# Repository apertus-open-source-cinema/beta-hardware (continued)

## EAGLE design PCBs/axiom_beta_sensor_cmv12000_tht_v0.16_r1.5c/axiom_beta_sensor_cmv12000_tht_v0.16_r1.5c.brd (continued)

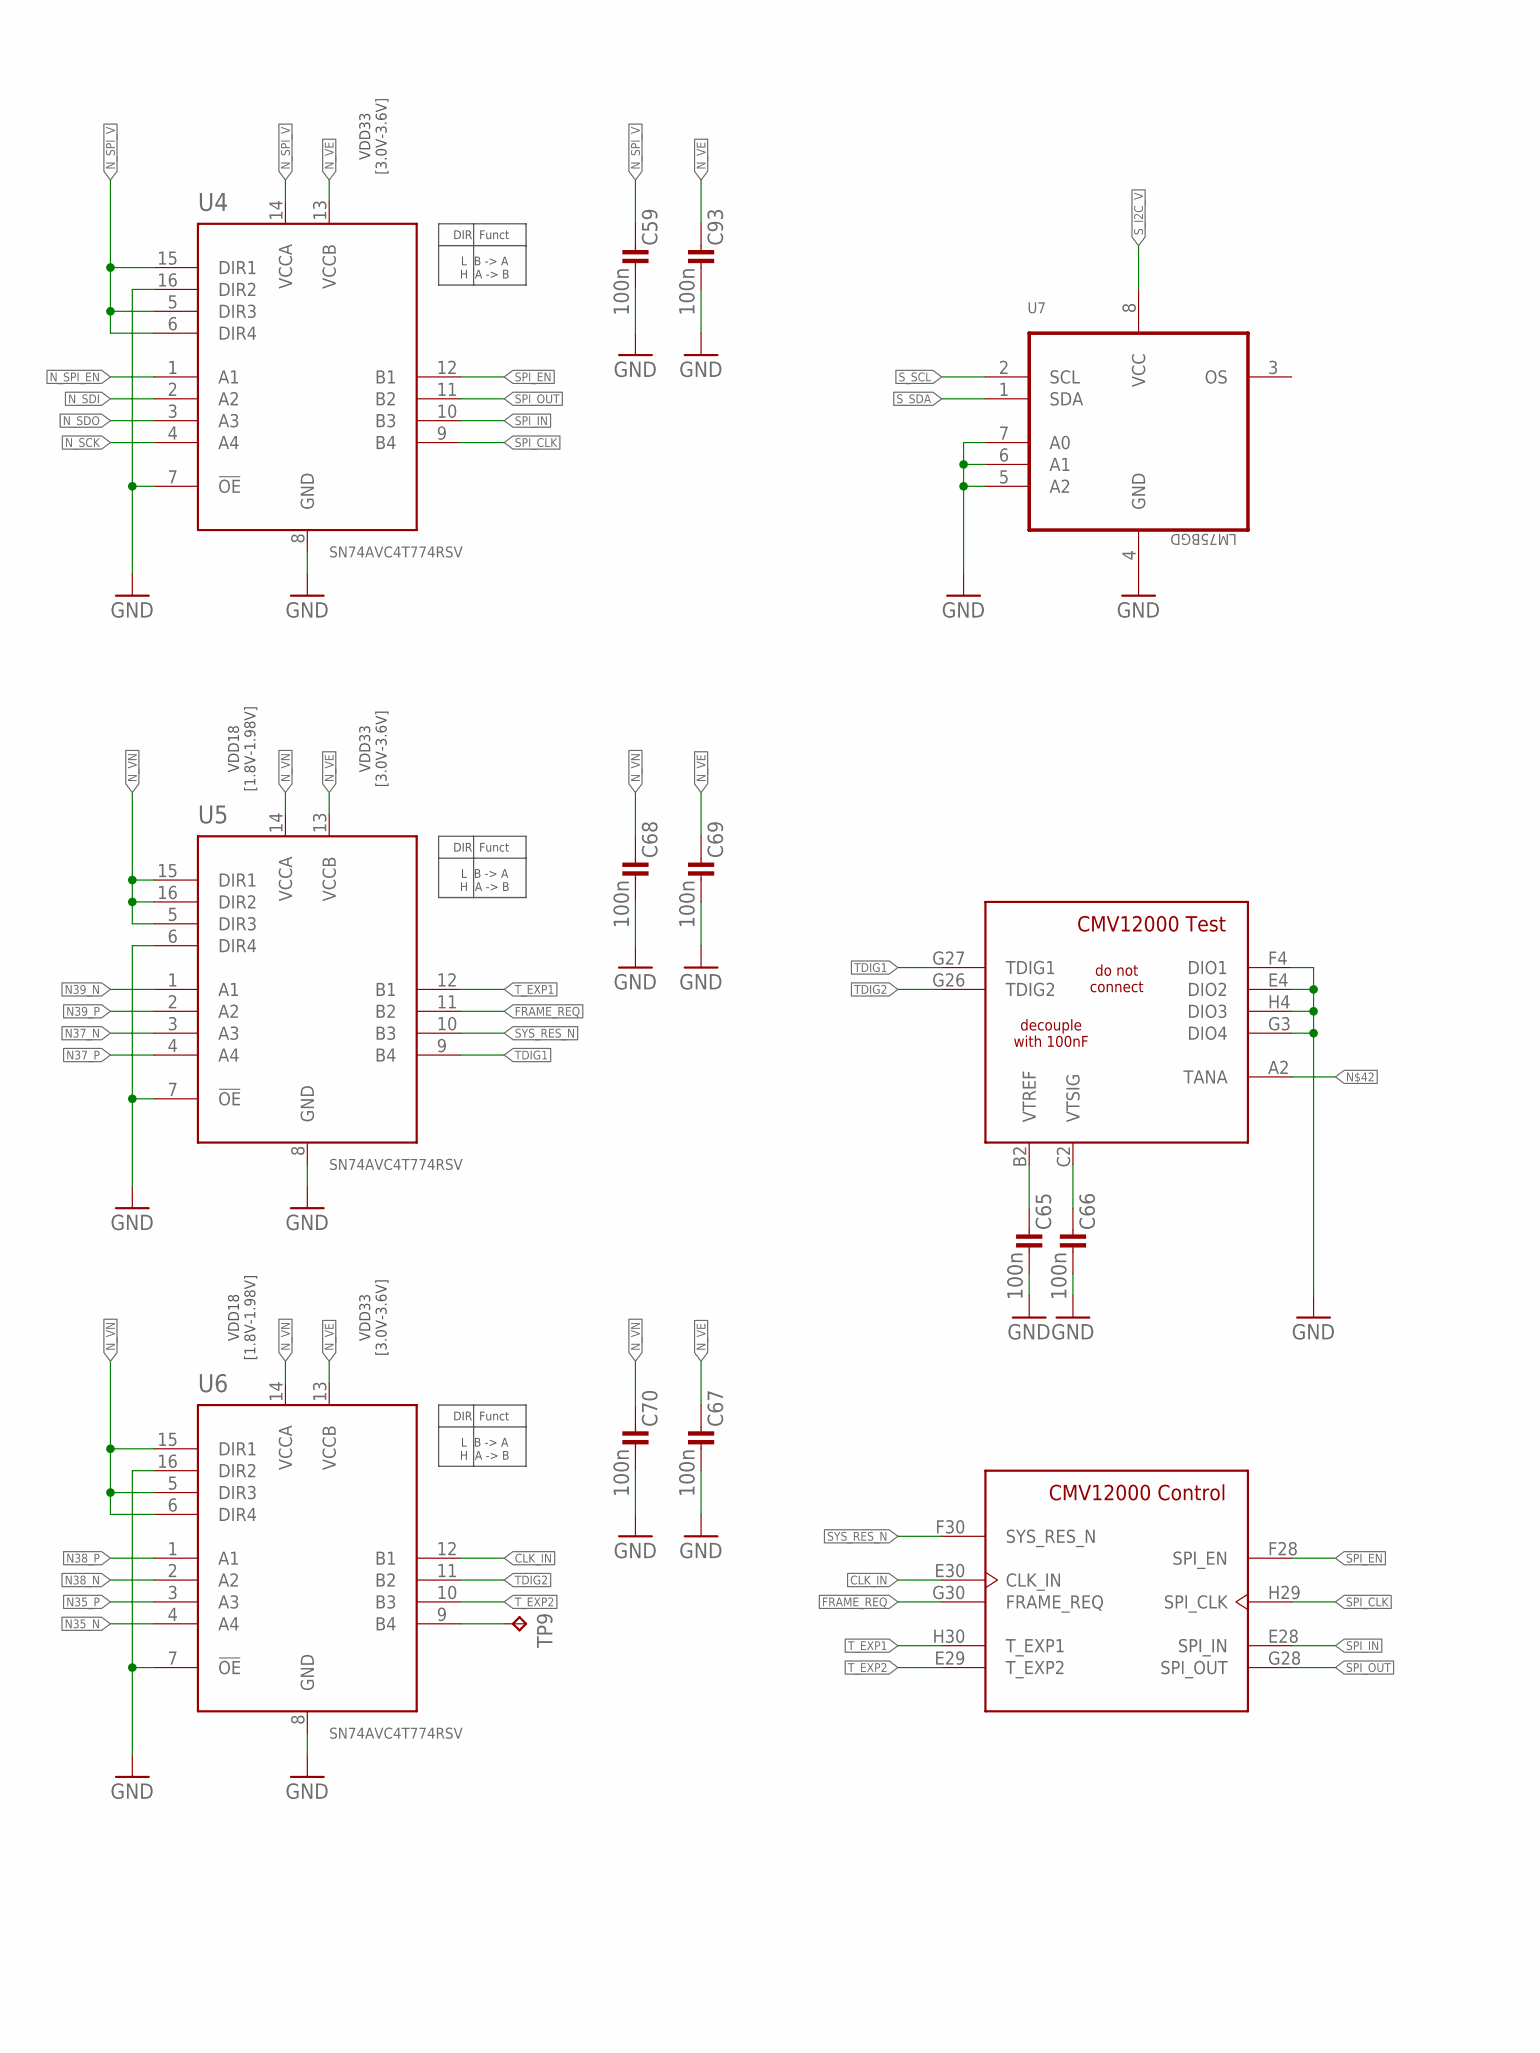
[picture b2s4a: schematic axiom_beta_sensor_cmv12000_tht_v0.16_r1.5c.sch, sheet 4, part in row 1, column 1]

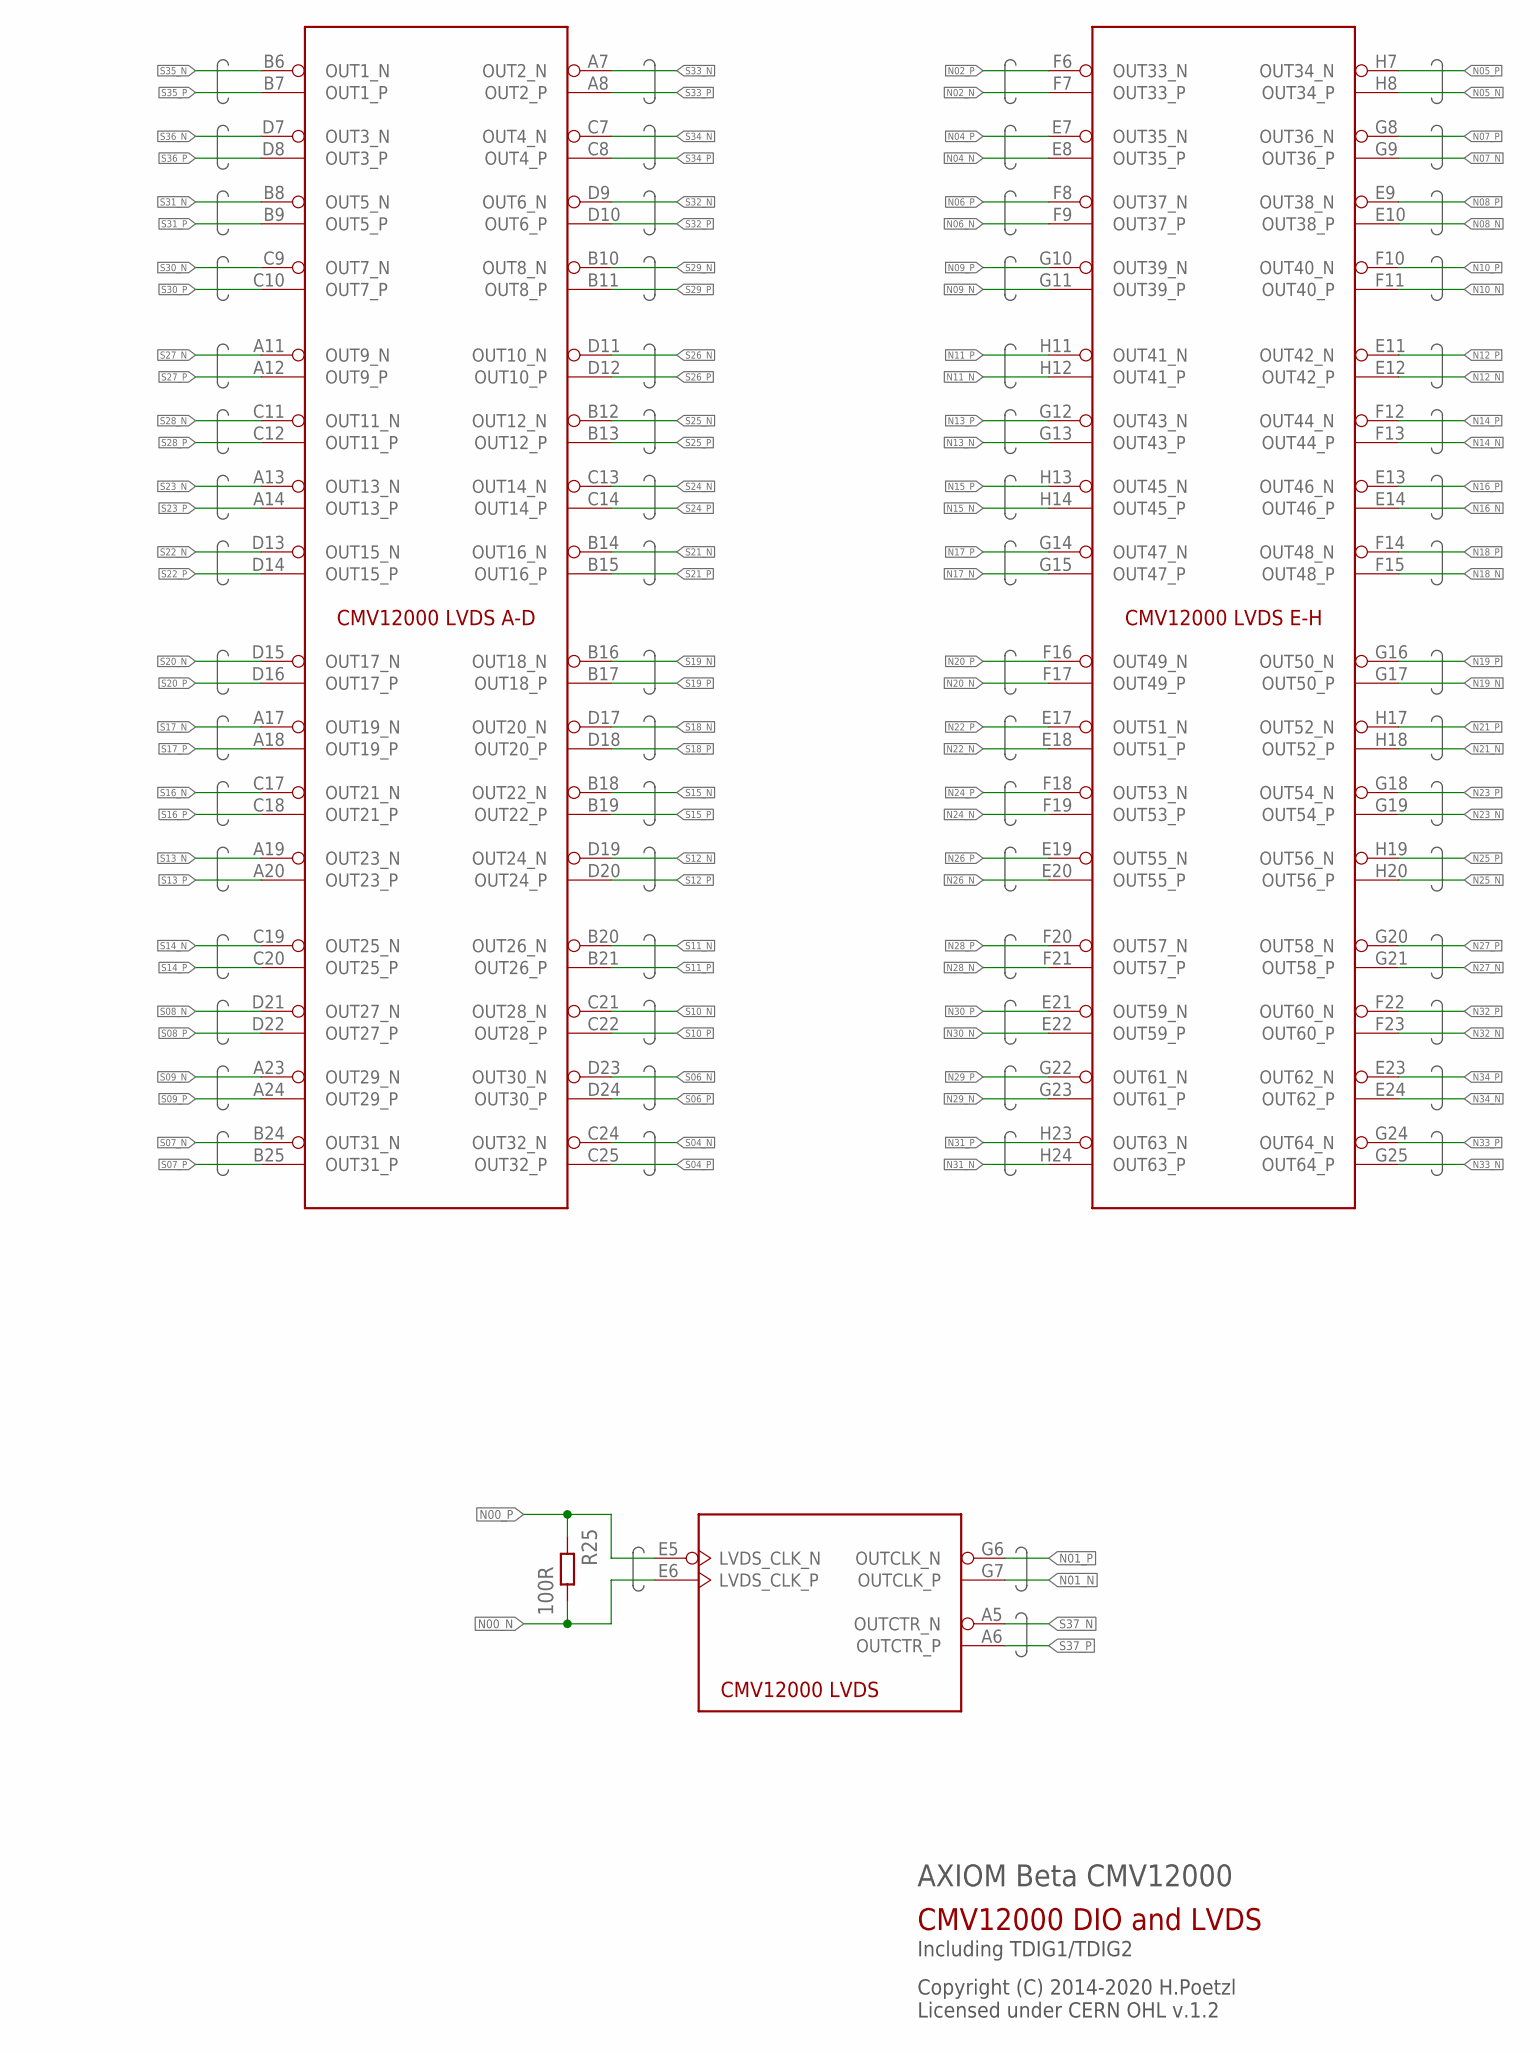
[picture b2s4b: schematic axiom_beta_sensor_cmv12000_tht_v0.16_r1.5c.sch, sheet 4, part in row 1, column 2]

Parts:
C59, C65, C66, C67, C68, C69, C70, C93: 100n; 0402-C
R25: 100R; 0402-C
SENSOR: CMV12000ANDON; 10-30-07-237-400T4
TP9: TPTP10R; TP10R
U4, U5, U6: SN74AVC4T774RSV; QFN40P185X265X55-16N
U7: LM75BGD; SOT996-2/3

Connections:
CLK_IN: SENSOR.E30 (CLK_IN), U6.12 (B1)
FRAME_REQ: SENSOR.G30 (FRAME_REQ), U5.11 (B2)
GND: C59.2, C65.2, C66.2, C67.2, C68.2, C69.2, C70.2, C93.2, SENSOR.E4 (DIO2), SENSOR.F4 (DIO1), SENSOR.G3 (DIO4), SENSOR.H4 (DIO3), U4.7 (!OE), U4.8 (GND), U4.16 (DIR2), U5.6 (DIR4), U5.7 (!OE), U5.8 (GND), U6.7 (!OE), U6.8 (GND), U6.16 (DIR2), U7.4 (GND), U7.5 (A2), U7.6 (A1), U7.7 (A0); also elsewhere on the board
N00_N: R25.2, SENSOR.E6 (LVDS_CLK_P); also elsewhere on the board
N00_P: R25.1, SENSOR.E5 (LVDS_CLK_N); also elsewhere on the board
N01_N: SENSOR.G7 (OUTCLK_P); also elsewhere on the board
N01_P: SENSOR.G6 (OUTCLK_N); also elsewhere on the board
N02_N: SENSOR.F7 (OUT33_P); also elsewhere on the board
N02_P: SENSOR.F6 (OUT33_N); also elsewhere on the board
N04_N: SENSOR.E8 (OUT35_P); also elsewhere on the board
N04_P: SENSOR.E7 (OUT35_N); also elsewhere on the board
N05_N: SENSOR.H8 (OUT34_P); also elsewhere on the board
N05_P: SENSOR.H7 (OUT34_N); also elsewhere on the board
N06_N: SENSOR.F9 (OUT37_P); also elsewhere on the board
N06_P: SENSOR.F8 (OUT37_N); also elsewhere on the board
N07_N: SENSOR.G9 (OUT36_P); also elsewhere on the board
N07_P: SENSOR.G8 (OUT36_N); also elsewhere on the board
N08_N: SENSOR.E10 (OUT38_P); also elsewhere on the board
N08_P: SENSOR.E9 (OUT38_N); also elsewhere on the board
N09_N: SENSOR.G11 (OUT39_P); also elsewhere on the board
N09_P: SENSOR.G10 (OUT39_N); also elsewhere on the board
N10_N: SENSOR.F11 (OUT40_P); also elsewhere on the board
N10_P: SENSOR.F10 (OUT40_N); also elsewhere on the board
N11_N: SENSOR.H12 (OUT41_P); also elsewhere on the board
N11_P: SENSOR.H11 (OUT41_N); also elsewhere on the board
N12_N: SENSOR.E12 (OUT42_P); also elsewhere on the board
N12_P: SENSOR.E11 (OUT42_N); also elsewhere on the board
N13_N: SENSOR.G13 (OUT43_P); also elsewhere on the board
N13_P: SENSOR.G12 (OUT43_N); also elsewhere on the board
N14_N: SENSOR.F13 (OUT44_P); also elsewhere on the board
N14_P: SENSOR.F12 (OUT44_N); also elsewhere on the board
N15_N: SENSOR.H14 (OUT45_P); also elsewhere on the board
N15_P: SENSOR.H13 (OUT45_N); also elsewhere on the board
N16_N: SENSOR.E14 (OUT46_P); also elsewhere on the board
N16_P: SENSOR.E13 (OUT46_N); also elsewhere on the board
N17_N: SENSOR.G15 (OUT47_P); also elsewhere on the board
N17_P: SENSOR.G14 (OUT47_N); also elsewhere on the board
N18_N: SENSOR.F15 (OUT48_P); also elsewhere on the board
N18_P: SENSOR.F14 (OUT48_N); also elsewhere on the board
N19_N: SENSOR.G17 (OUT50_P); also elsewhere on the board
N19_P: SENSOR.G16 (OUT50_N); also elsewhere on the board
N20_N: SENSOR.F17 (OUT49_P); also elsewhere on the board
N20_P: SENSOR.F16 (OUT49_N); also elsewhere on the board
N21_N: SENSOR.H18 (OUT52_P); also elsewhere on the board
N21_P: SENSOR.H17 (OUT52_N); also elsewhere on the board
N22_N: SENSOR.E18 (OUT51_P); also elsewhere on the board
N22_P: SENSOR.E17 (OUT51_N); also elsewhere on the board
N23_N: SENSOR.G19 (OUT54_P); also elsewhere on the board
N23_P: SENSOR.G18 (OUT54_N); also elsewhere on the board
N24_N: SENSOR.F19 (OUT53_P); also elsewhere on the board
N24_P: SENSOR.F18 (OUT53_N); also elsewhere on the board
N25_N: SENSOR.H20 (OUT56_P); also elsewhere on the board
N25_P: SENSOR.H19 (OUT56_N); also elsewhere on the board
N26_N: SENSOR.E20 (OUT55_P); also elsewhere on the board
N26_P: SENSOR.E19 (OUT55_N); also elsewhere on the board
N27_N: SENSOR.G21 (OUT58_P); also elsewhere on the board
N27_P: SENSOR.G20 (OUT58_N); also elsewhere on the board
N28_N: SENSOR.F21 (OUT57_P); also elsewhere on the board
N28_P: SENSOR.F20 (OUT57_N); also elsewhere on the board
N29_N: SENSOR.G23 (OUT61_P); also elsewhere on the board
N29_P: SENSOR.G22 (OUT61_N); also elsewhere on the board
N30_N: SENSOR.E22 (OUT59_P); also elsewhere on the board
N30_P: SENSOR.E21 (OUT59_N); also elsewhere on the board
N31_N: SENSOR.H24 (OUT63_P); also elsewhere on the board
N31_P: SENSOR.H23 (OUT63_N); also elsewhere on the board
N32_N: SENSOR.F23 (OUT60_P); also elsewhere on the board
N32_P: SENSOR.F22 (OUT60_N); also elsewhere on the board
N33_N: SENSOR.G25 (OUT64_P); also elsewhere on the board
N33_P: SENSOR.G24 (OUT64_N); also elsewhere on the board
N34_N: SENSOR.E24 (OUT62_P); also elsewhere on the board
N34_P: SENSOR.E23 (OUT62_N); also elsewhere on the board
N35_N: U6.4 (A4); also elsewhere on the board
N35_P: U6.3 (A3); also elsewhere on the board
N37_N: U5.3 (A3); also elsewhere on the board
N37_P: U5.4 (A4); also elsewhere on the board
N38_N: U6.2 (A2); also elsewhere on the board
N38_P: U6.1 (A1); also elsewhere on the board
N39_N: U5.1 (A1); also elsewhere on the board
N39_P: U5.2 (A2); also elsewhere on the board
unnamed: TP9.TP, U6.9 (B4)
N_SCK: U4.4 (A4); also elsewhere on the board
N_SDI: U4.2 (A2); also elsewhere on the board
N_SDO: U4.3 (A3); also elsewhere on the board
N_SPI_EN: U4.1 (A1); also elsewhere on the board
N_SPI_V: C59.1, U4.5 (DIR3), U4.6 (DIR4), U4.14 (VCCA), U4.15 (DIR1); also elsewhere on the board
N_VE: C67.1, C69.1, C93.1, U4.13 (VCCB), U5.13 (VCCB), U6.13 (VCCB); also elsewhere on the board
N_VN: C68.1, C70.1, U5.5 (DIR3), U5.14 (VCCA), U5.15 (DIR1), U5.16 (DIR2), U6.5 (DIR3), U6.6 (DIR4), U6.14 (VCCA), U6.15 (DIR1); also elsewhere on the board
S04_N: SENSOR.C24 (OUT32_N); also elsewhere on the board
S04_P: SENSOR.C25 (OUT32_P); also elsewhere on the board
S06_N: SENSOR.D23 (OUT30_N); also elsewhere on the board
S06_P: SENSOR.D24 (OUT30_P); also elsewhere on the board
S07_N: SENSOR.B24 (OUT31_N); also elsewhere on the board
S07_P: SENSOR.B25 (OUT31_P); also elsewhere on the board
S08_N: SENSOR.D21 (OUT27_N); also elsewhere on the board
S08_P: SENSOR.D22 (OUT27_P); also elsewhere on the board
S09_N: SENSOR.A23 (OUT29_N); also elsewhere on the board
S09_P: SENSOR.A24 (OUT29_P); also elsewhere on the board
S10_N: SENSOR.C21 (OUT28_N); also elsewhere on the board
S10_P: SENSOR.C22 (OUT28_P); also elsewhere on the board
S11_N: SENSOR.B20 (OUT26_N); also elsewhere on the board
S11_P: SENSOR.B21 (OUT26_P); also elsewhere on the board
S12_N: SENSOR.D19 (OUT24_N); also elsewhere on the board
S12_P: SENSOR.D20 (OUT24_P); also elsewhere on the board
S13_N: SENSOR.A19 (OUT23_N); also elsewhere on the board
S13_P: SENSOR.A20 (OUT23_P); also elsewhere on the board
S14_N: SENSOR.C19 (OUT25_N); also elsewhere on the board
S14_P: SENSOR.C20 (OUT25_P); also elsewhere on the board
S15_N: SENSOR.B18 (OUT22_N); also elsewhere on the board
S15_P: SENSOR.B19 (OUT22_P); also elsewhere on the board
S16_N: SENSOR.C17 (OUT21_N); also elsewhere on the board
S16_P: SENSOR.C18 (OUT21_P); also elsewhere on the board
S17_N: SENSOR.A17 (OUT19_N); also elsewhere on the board
S17_P: SENSOR.A18 (OUT19_P); also elsewhere on the board
S18_N: SENSOR.D17 (OUT20_N); also elsewhere on the board
S18_P: SENSOR.D18 (OUT20_P); also elsewhere on the board
S19_N: SENSOR.B16 (OUT18_N); also elsewhere on the board
S19_P: SENSOR.B17 (OUT18_P); also elsewhere on the board
S20_N: SENSOR.D15 (OUT17_N); also elsewhere on the board
S20_P: SENSOR.D16 (OUT17_P); also elsewhere on the board
S21_N: SENSOR.B14 (OUT16_N); also elsewhere on the board
S21_P: SENSOR.B15 (OUT16_P); also elsewhere on the board
S22_N: SENSOR.D13 (OUT15_N); also elsewhere on the board
S22_P: SENSOR.D14 (OUT15_P); also elsewhere on the board
S23_N: SENSOR.A13 (OUT13_N); also elsewhere on the board
S23_P: SENSOR.A14 (OUT13_P); also elsewhere on the board
S24_N: SENSOR.C13 (OUT14_N); also elsewhere on the board
S24_P: SENSOR.C14 (OUT14_P); also elsewhere on the board
S25_N: SENSOR.B12 (OUT12_N); also elsewhere on the board
S25_P: SENSOR.B13 (OUT12_P); also elsewhere on the board
S26_N: SENSOR.D11 (OUT10_N); also elsewhere on the board
S26_P: SENSOR.D12 (OUT10_P); also elsewhere on the board
S27_N: SENSOR.A11 (OUT9_N); also elsewhere on the board
S27_P: SENSOR.A12 (OUT9_P); also elsewhere on the board
S28_N: SENSOR.C11 (OUT11_N); also elsewhere on the board
S28_P: SENSOR.C12 (OUT11_P); also elsewhere on the board
S29_N: SENSOR.B10 (OUT8_N); also elsewhere on the board
S29_P: SENSOR.B11 (OUT8_P); also elsewhere on the board
S30_N: SENSOR.C9 (OUT7_N); also elsewhere on the board
S30_P: SENSOR.C10 (OUT7_P); also elsewhere on the board
S31_N: SENSOR.B8 (OUT5_N); also elsewhere on the board
S31_P: SENSOR.B9 (OUT5_P); also elsewhere on the board
S32_N: SENSOR.D9 (OUT6_N); also elsewhere on the board
S32_P: SENSOR.D10 (OUT6_P); also elsewhere on the board
S33_N: SENSOR.A7 (OUT2_N); also elsewhere on the board
S33_P: SENSOR.A8 (OUT2_P); also elsewhere on the board
S34_N: SENSOR.C7 (OUT4_N); also elsewhere on the board
S34_P: SENSOR.C8 (OUT4_P); also elsewhere on the board
S35_N: SENSOR.B6 (OUT1_N); also elsewhere on the board
S35_P: SENSOR.B7 (OUT1_P); also elsewhere on the board
S36_N: SENSOR.D7 (OUT3_N); also elsewhere on the board
S36_P: SENSOR.D8 (OUT3_P); also elsewhere on the board
S37_N: SENSOR.A5 (OUTCTR_N); also elsewhere on the board
S37_P: SENSOR.A6 (OUTCTR_P); also elsewhere on the board
SPI_CLK: SENSOR.H29 (SPI_CLK), U4.9 (B4)
SPI_EN: SENSOR.F28 (SPI_EN), U4.12 (B1)
SPI_IN: SENSOR.E28 (SPI_IN), U4.10 (B3)
SPI_OUT: SENSOR.G28 (SPI_OUT), U4.11 (B2)
SYS_RES_N: SENSOR.F30 (SYS_RES_N), U5.10 (B3)
S_I2C_V: U7.8 (VCC); also elsewhere on the board
S_SCL: U7.2 (SCL); also elsewhere on the board
S_SDA: U7.1 (SDA); also elsewhere on the board
TDIG1: SENSOR.G27 (TDIG1), U5.9 (B4)
TDIG2: SENSOR.G26 (TDIG2), U6.11 (B2)
T_EXP1: SENSOR.H30 (T_EXP1), U5.12 (B1)
T_EXP2: SENSOR.E29 (T_EXP2), U6.10 (B3)
VTREF: C65.1, SENSOR.B2 (VTREF); also elsewhere on the board
VTSIG: C66.1, SENSOR.C2 (VTSIG); also elsewhere on the board

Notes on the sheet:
AXIOM Beta CMV12000
Copyright (C) 2014-2020 H.Poetzl Licensed under CERN OHL v.1.2
CMV12000 DIO and LVDS
Including TDIG1/TDIG2
DIR Funct L B -> A H A -> B
VDD18 [1.8V-1.98V]
VDD33 [3.0V-3.6V]

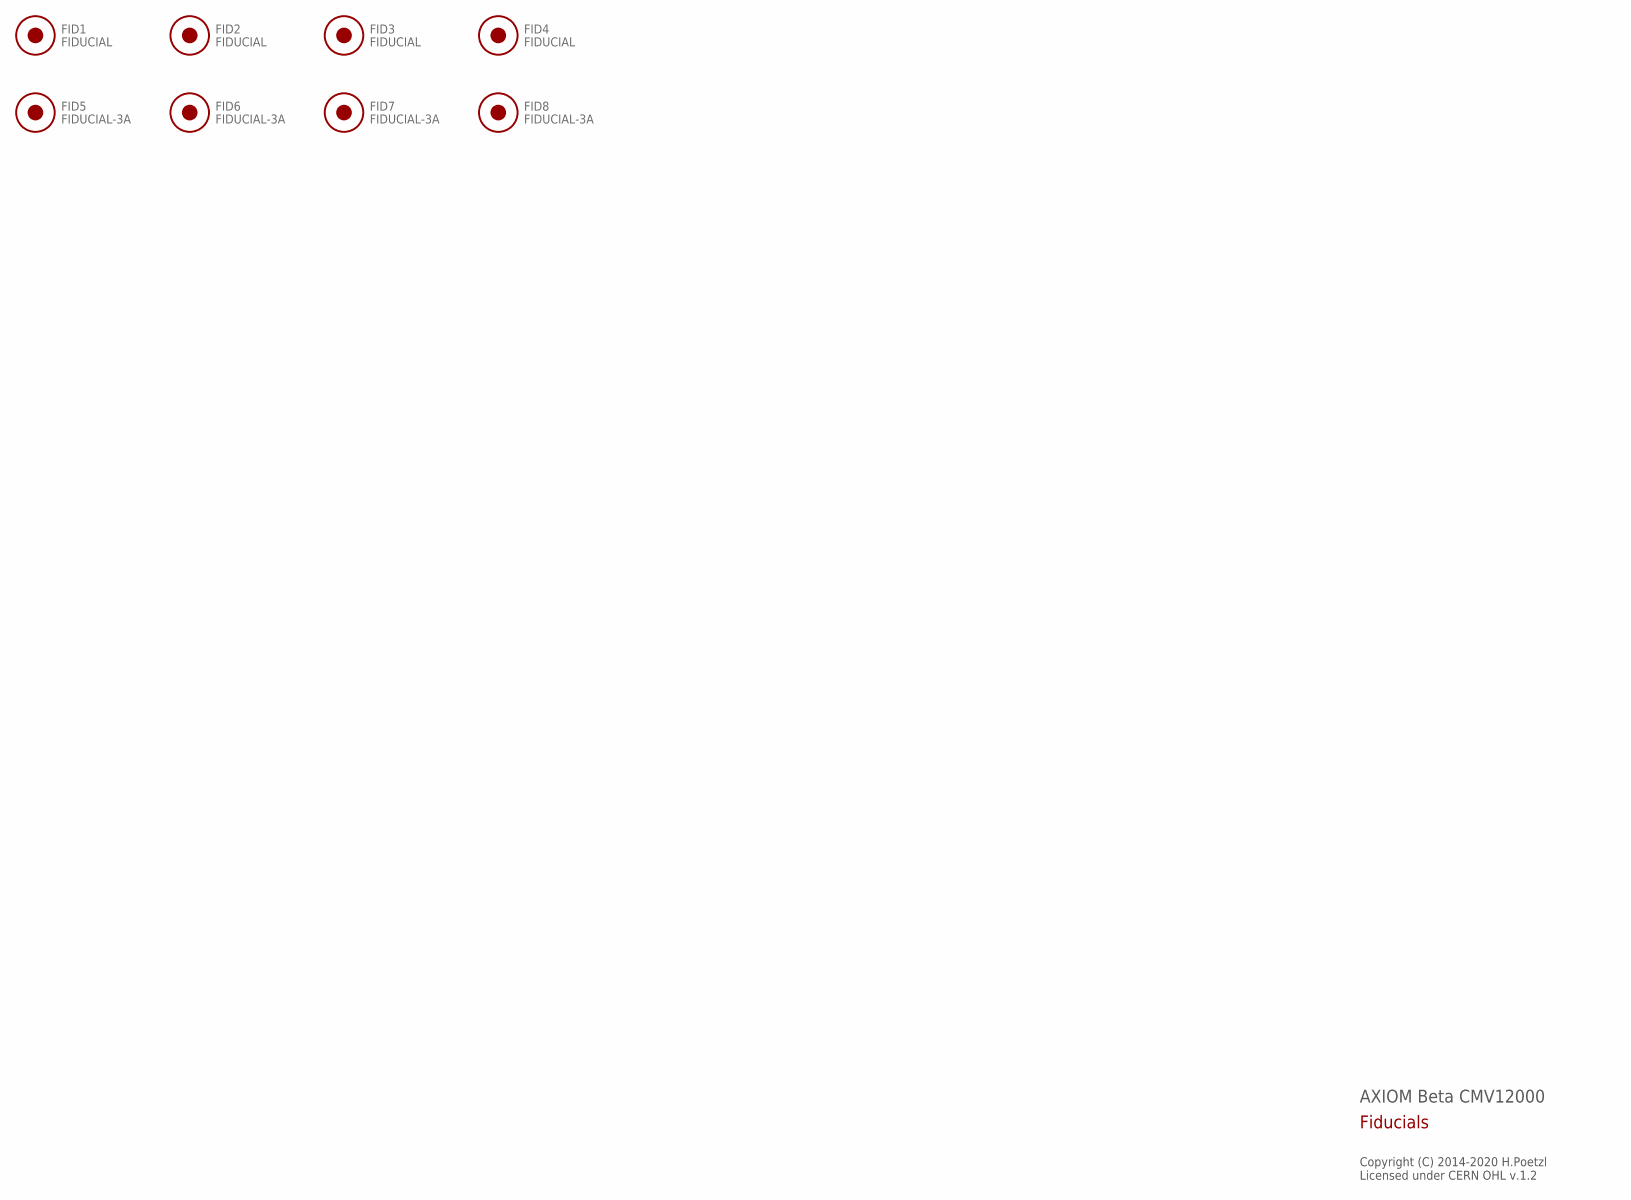
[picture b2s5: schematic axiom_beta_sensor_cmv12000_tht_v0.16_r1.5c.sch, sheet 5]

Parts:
FID1, FID2, FID3, FID4: FIDUCIAL; FID_ARROW
FID5, FID6, FID7, FID8: FIDUCIAL-3A; FID_3ARROW

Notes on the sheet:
AXIOM Beta CMV12000
Copyright (C) 2014-2020 H.Poetzl Licensed under CERN OHL v.1.2
Fiducials

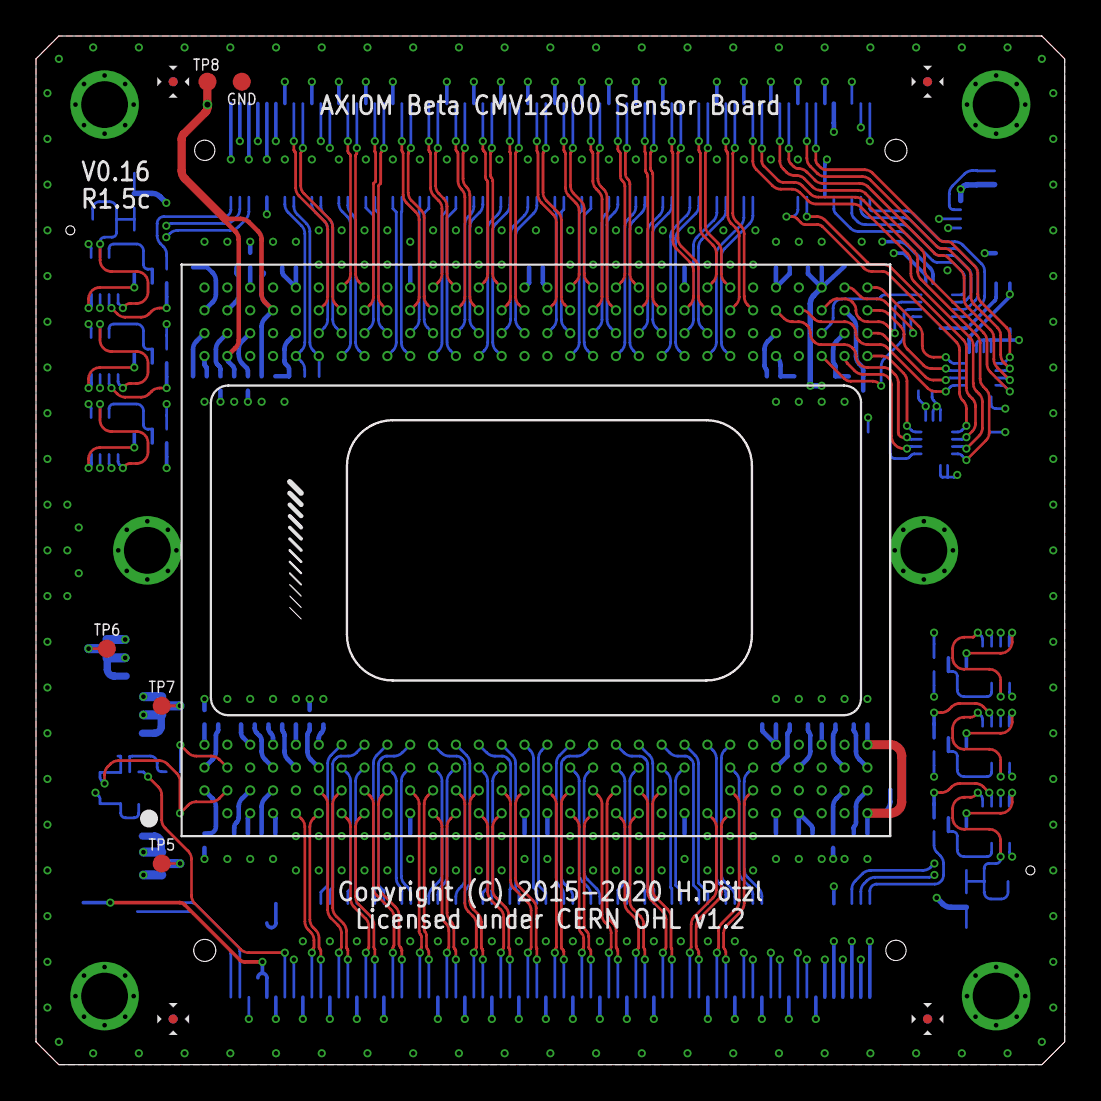
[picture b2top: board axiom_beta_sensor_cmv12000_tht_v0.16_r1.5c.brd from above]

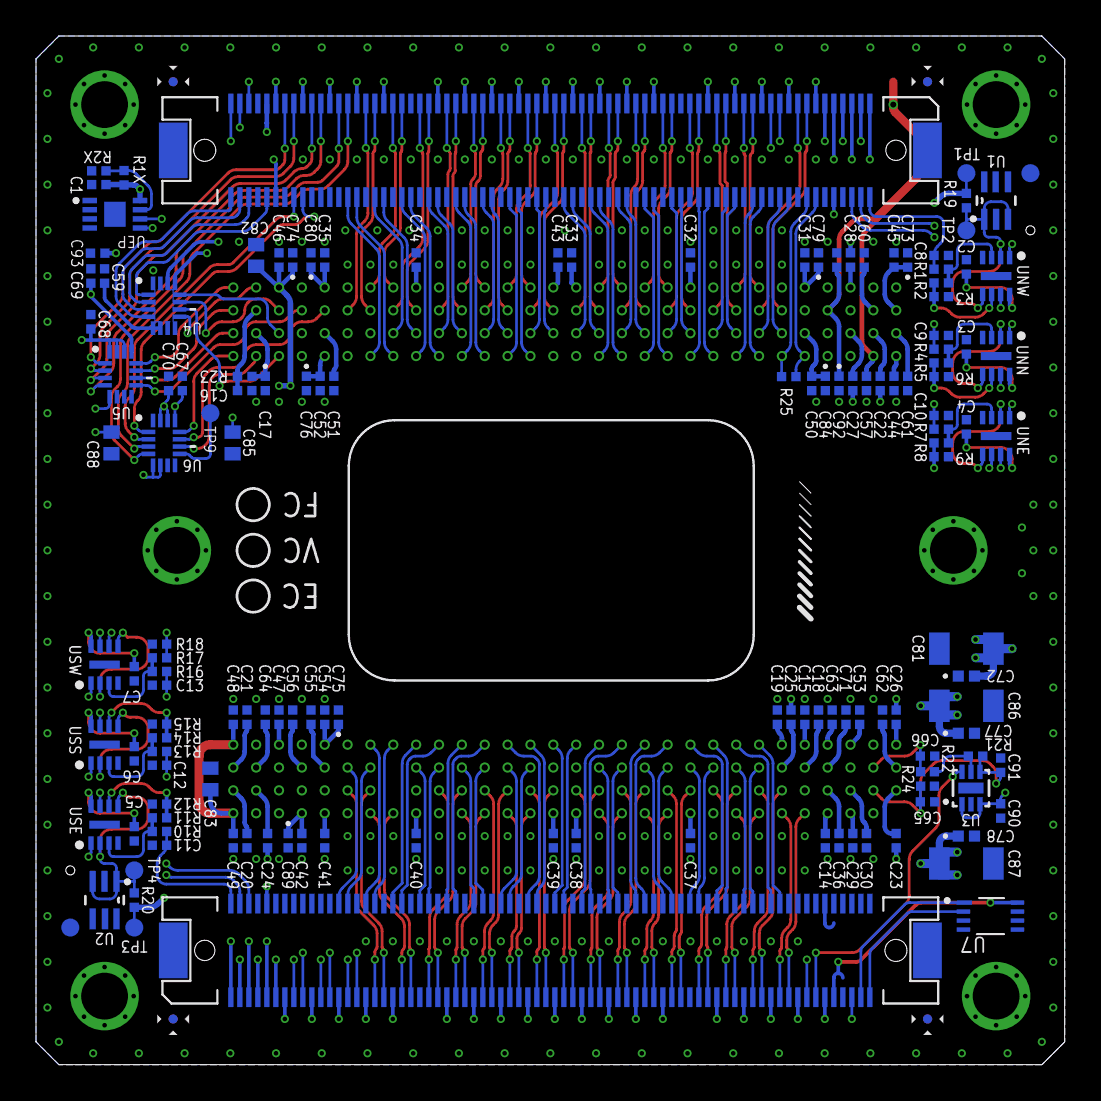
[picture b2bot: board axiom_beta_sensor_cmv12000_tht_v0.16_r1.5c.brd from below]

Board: 4 copper layers, 57.1 x 57.1 mm, 159 parts (147 on the bottom side), 234 nets.

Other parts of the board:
PARALLELLA: PARALLELLA-FRAME
U$1: µZ-FRAME

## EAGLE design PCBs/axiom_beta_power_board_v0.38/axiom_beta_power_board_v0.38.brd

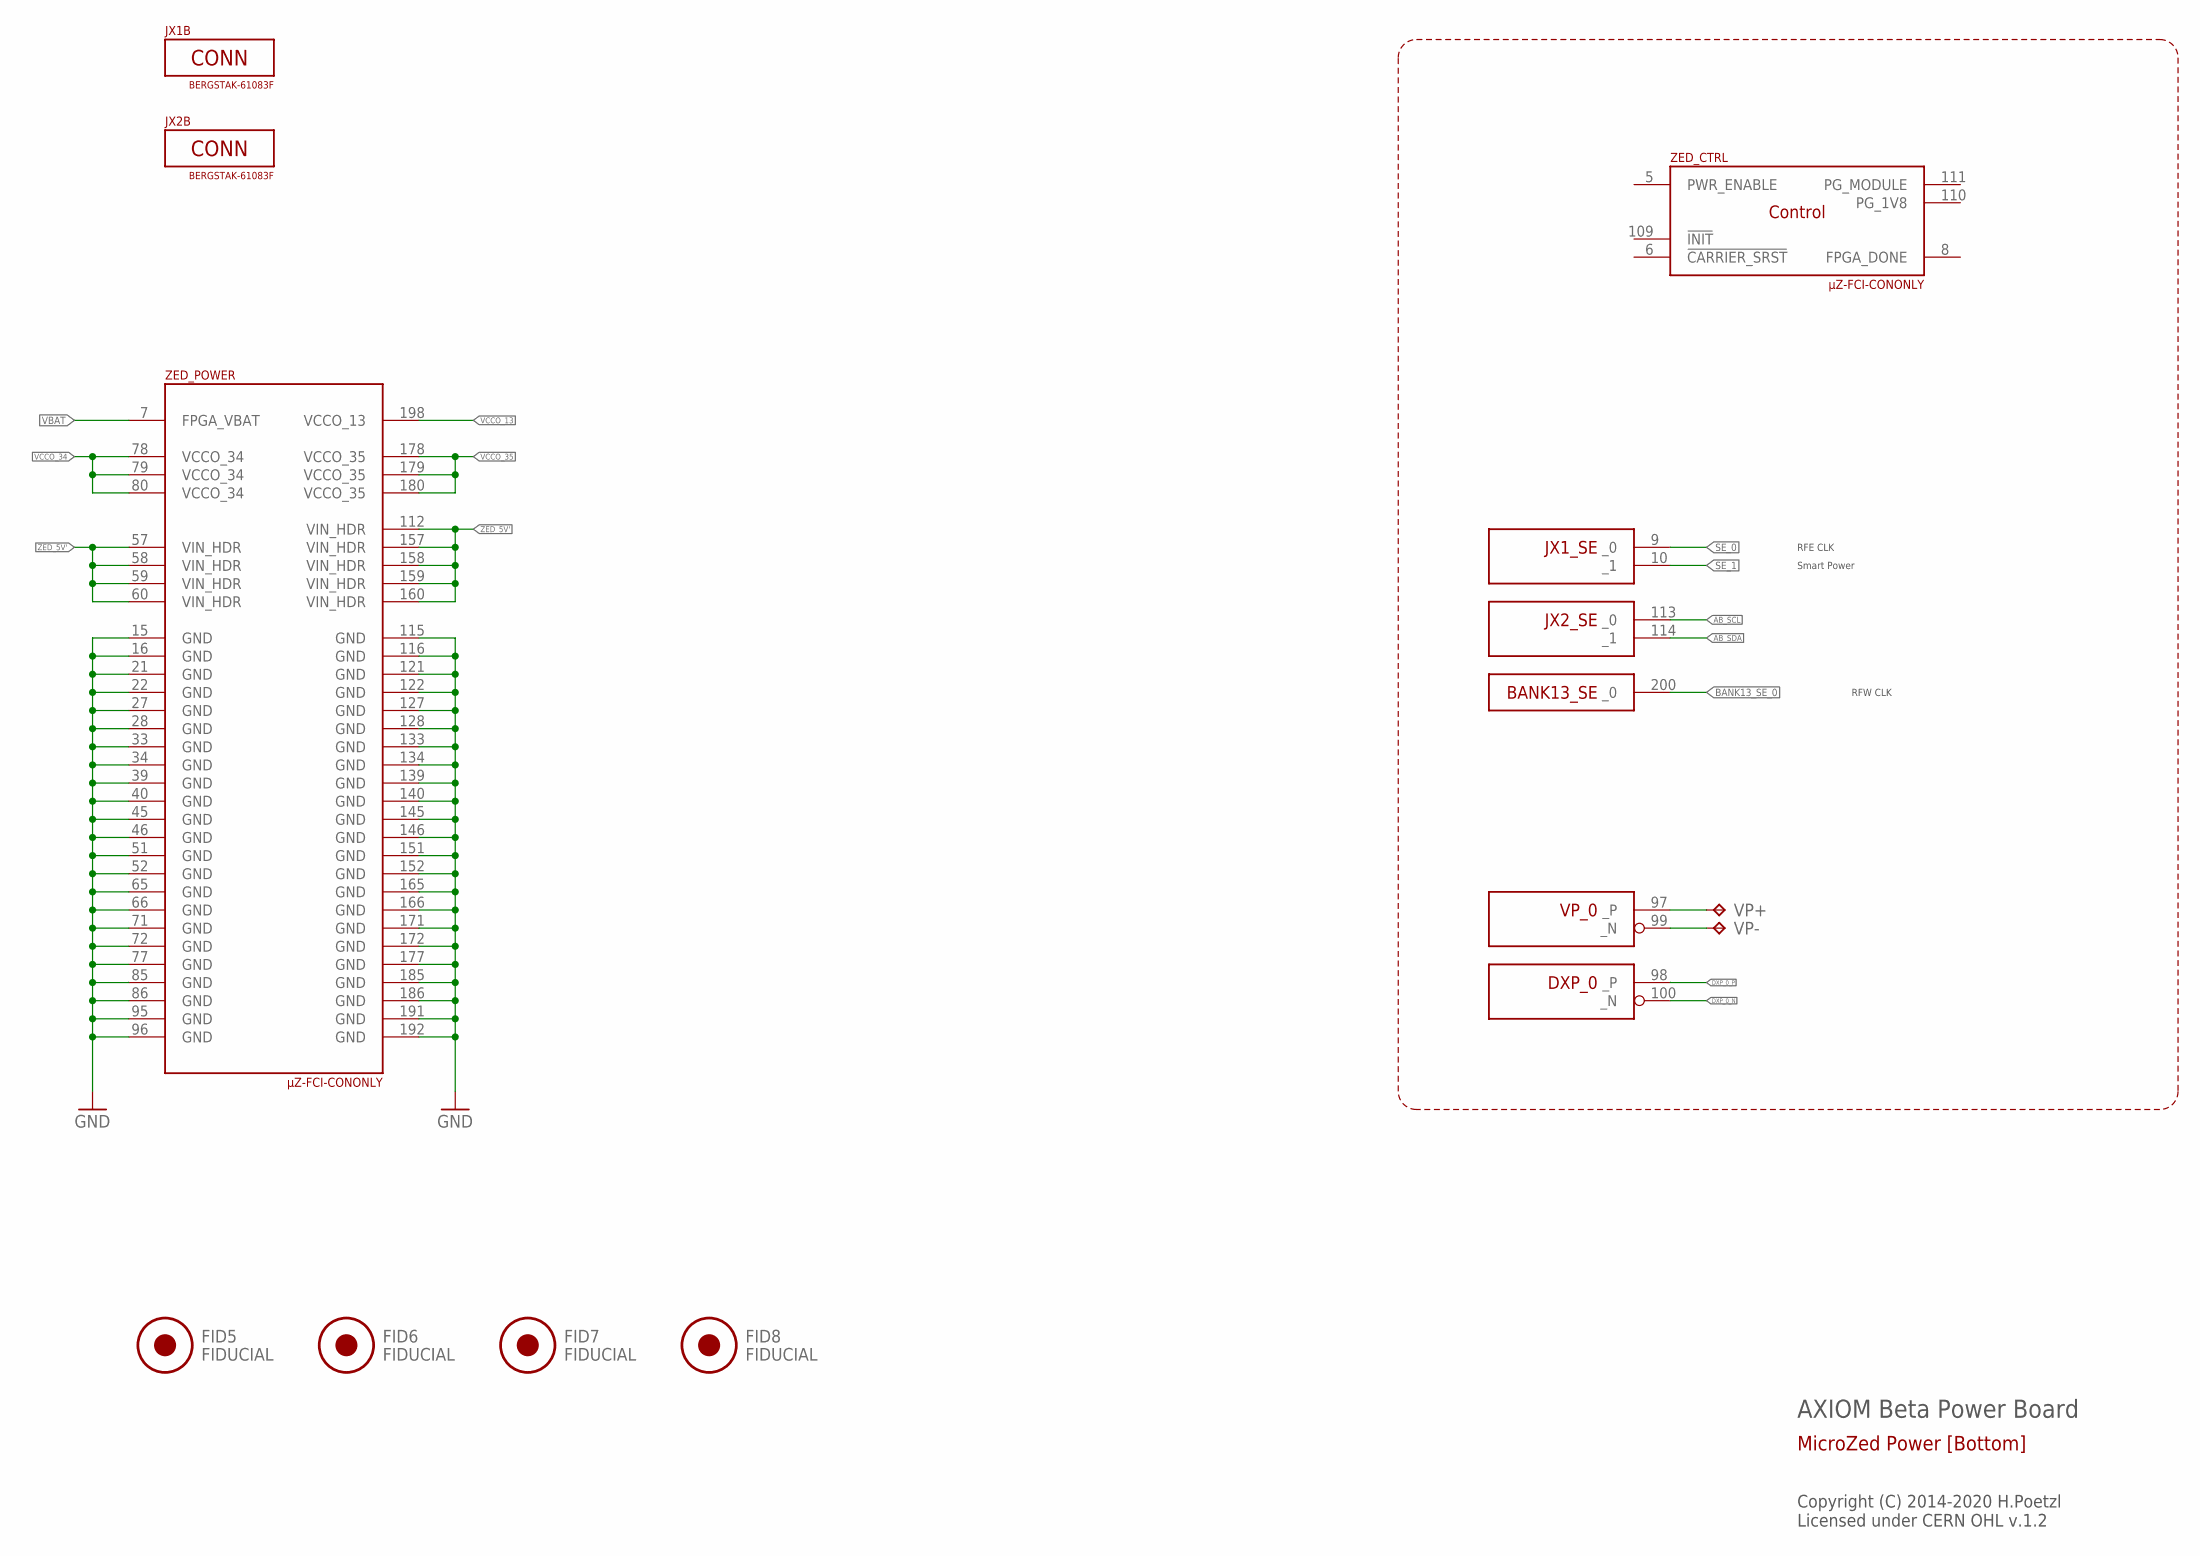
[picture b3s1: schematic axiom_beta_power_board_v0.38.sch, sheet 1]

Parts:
FID5, FID6, FID7, FID8: FIDUCIAL; FID_ARROW
JX1B, JX2B: BERGSTAK-61083F; 61083-FAKE
VP+: TPTP16SQ; TP16SQ
VP-: TPTP16SQ; TP16SQ
ZED: µZ-FCI-CONONLY; µZ-CONONLY

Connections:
AB_SCL: ZED.113 (_0); also elsewhere on the board
AB_SDA: ZED.114 (_1); also elsewhere on the board
BANK13_SE_0: ZED.200 (_0); also elsewhere on the board
DXP_0_N: ZED.100 (_N)
DXP_0_P: ZED.98 (_P)
GND: ZED.15 (GND), ZED.16 (GND), ZED.21 (GND), ZED.22 (GND), ZED.27 (GND), ZED.28 (GND), ZED.33 (GND), ZED.34 (GND), ZED.39 (GND), ZED.40 (GND), ZED.45 (GND), ZED.46 (GND), ZED.51 (GND), ZED.52 (GND), ZED.65 (GND), ZED.66 (GND), ZED.71 (GND), ZED.72 (GND), ZED.77 (GND), ZED.85 (GND), ZED.86 (GND), ZED.95 (GND), ZED.96 (GND), ZED.115 (GND), ZED.116 (GND), ZED.121 (GND), ZED.122 (GND), ZED.127 (GND), ZED.128 (GND), ZED.133 (GND), ZED.134 (GND), ZED.139 (GND), ZED.140 (GND), ZED.145 (GND), ZED.146 (GND), ZED.151 (GND), ZED.152 (GND), ZED.165 (GND), ZED.166 (GND), ZED.171 (GND), ZED.172 (GND), ZED.177 (GND), ZED.185 (GND), ZED.186 (GND), ZED.191 (GND), ZED.192 (GND); also elsewhere on the board
SE_0: ZED.9 (_0); also elsewhere on the board
SE_1: ZED.10 (_1); also elsewhere on the board
VBAT: ZED.7 (FPGA_VBAT)
VCCO_13: ZED.198 (VCCO_13); also elsewhere on the board
VCCO_34: ZED.78 (VCCO_34), ZED.79 (VCCO_34), ZED.80 (VCCO_34); also elsewhere on the board
VCCO_35: ZED.178 (VCCO_35), ZED.179 (VCCO_35), ZED.180 (VCCO_35); also elsewhere on the board
VP_0_N: VP-.TP, ZED.99 (_N)
VP_0_P: VP+.TP, ZED.97 (_P)
ZED_5V': ZED.57 (VIN_HDR), ZED.58 (VIN_HDR), ZED.59 (VIN_HDR), ZED.60 (VIN_HDR), ZED.112 (VIN_HDR), ZED.157 (VIN_HDR), ZED.158 (VIN_HDR), ZED.159 (VIN_HDR), ZED.160 (VIN_HDR); also elsewhere on the board

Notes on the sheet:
AXIOM Beta Power Board
Copyright (C) 2014-2020 H.Poetzl Licensed under CERN OHL v.1.2
MicroZed Power [Bottom]
Smart Power
RFE CLK
RFW CLK
